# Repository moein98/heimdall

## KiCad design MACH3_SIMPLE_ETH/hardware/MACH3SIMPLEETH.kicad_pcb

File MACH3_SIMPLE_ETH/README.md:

# MACH3-SIMPLE-ETH (draft 0)

MACH3-SIMPLE with Ethernet instead of the parallel ports: an RP2350B runs
grblHAL on the board, eight independent coordinated axes, W5500 Ethernet,
the A1 relays, inputs and isolated VFD port, plus RS485 Modbus, SD card and
a web UI served by the board.

So far: architecture and pin map (`docs/SPEC.md`), a grblHAL build that
proves the pin map, and the schematic (ERC clean, checked against the
firmware's pin map). No board layout yet.

| Folder | What is in it |
|---|---|
| `docs/SPEC.md` | the design, the RP2350B pin map, circuit notes, schematic status |
| `hardware/` | KiCad 10 schematic, 8 sheets - generated, do not edit by hand |
| `tools/` | `build_project.py` (generates the schematic), `check_pinmap.py`, `validate.sh` |
| `review/` | ERC report, netlist, schematic PDF, BOM |
| `firmware/grblHAL/` | board map, `my_machine.h` and CMake patches, `build.sh` |
| `firmware/remora/` | a three-line patch that builds Remora (LinuxCNC) for RP2350 - untested |

    PICO_SDK_PATH=/path/to/pico-sdk sh firmware/grblHAL/build.sh

    python3 tools/build_project.py     # KICAD_SYMBOL_DIR = KiCad's symbol library
    KICAD_CLI=kicad-cli sh tools/validate.sh

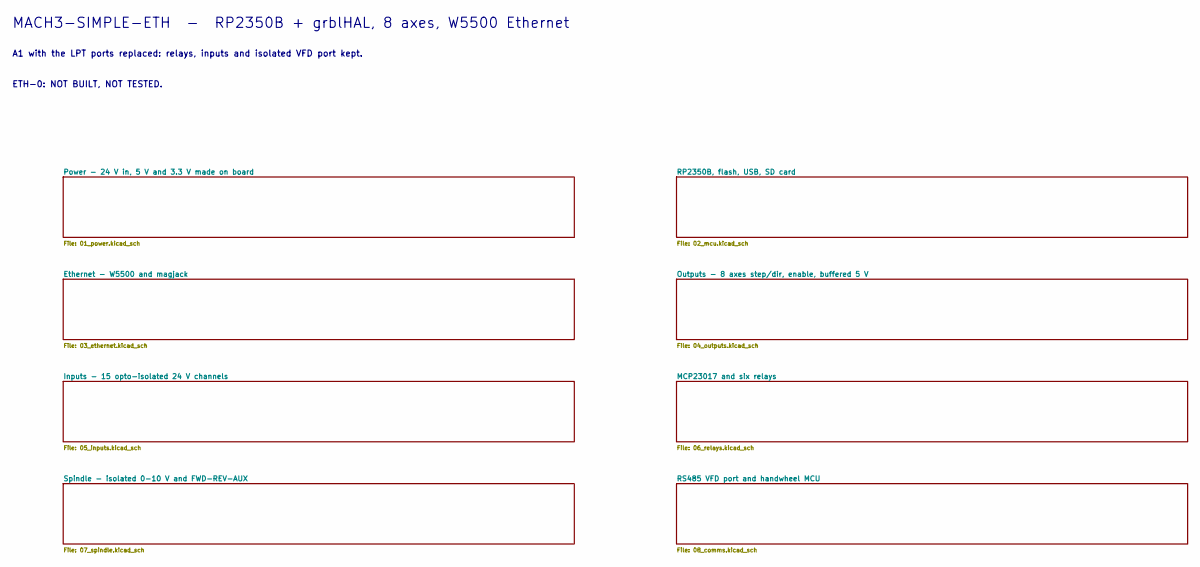
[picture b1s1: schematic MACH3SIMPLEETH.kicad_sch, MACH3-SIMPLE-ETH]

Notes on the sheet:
MACH3-SIMPLE-ETH - RP2350B + grblHAL, 8 axes, W5500 Ethernet
A1 with the LPT ports replaced: relays, inputs and isolated VFD port kept.
ETH-0: NOT BUILT, NOT TESTED.

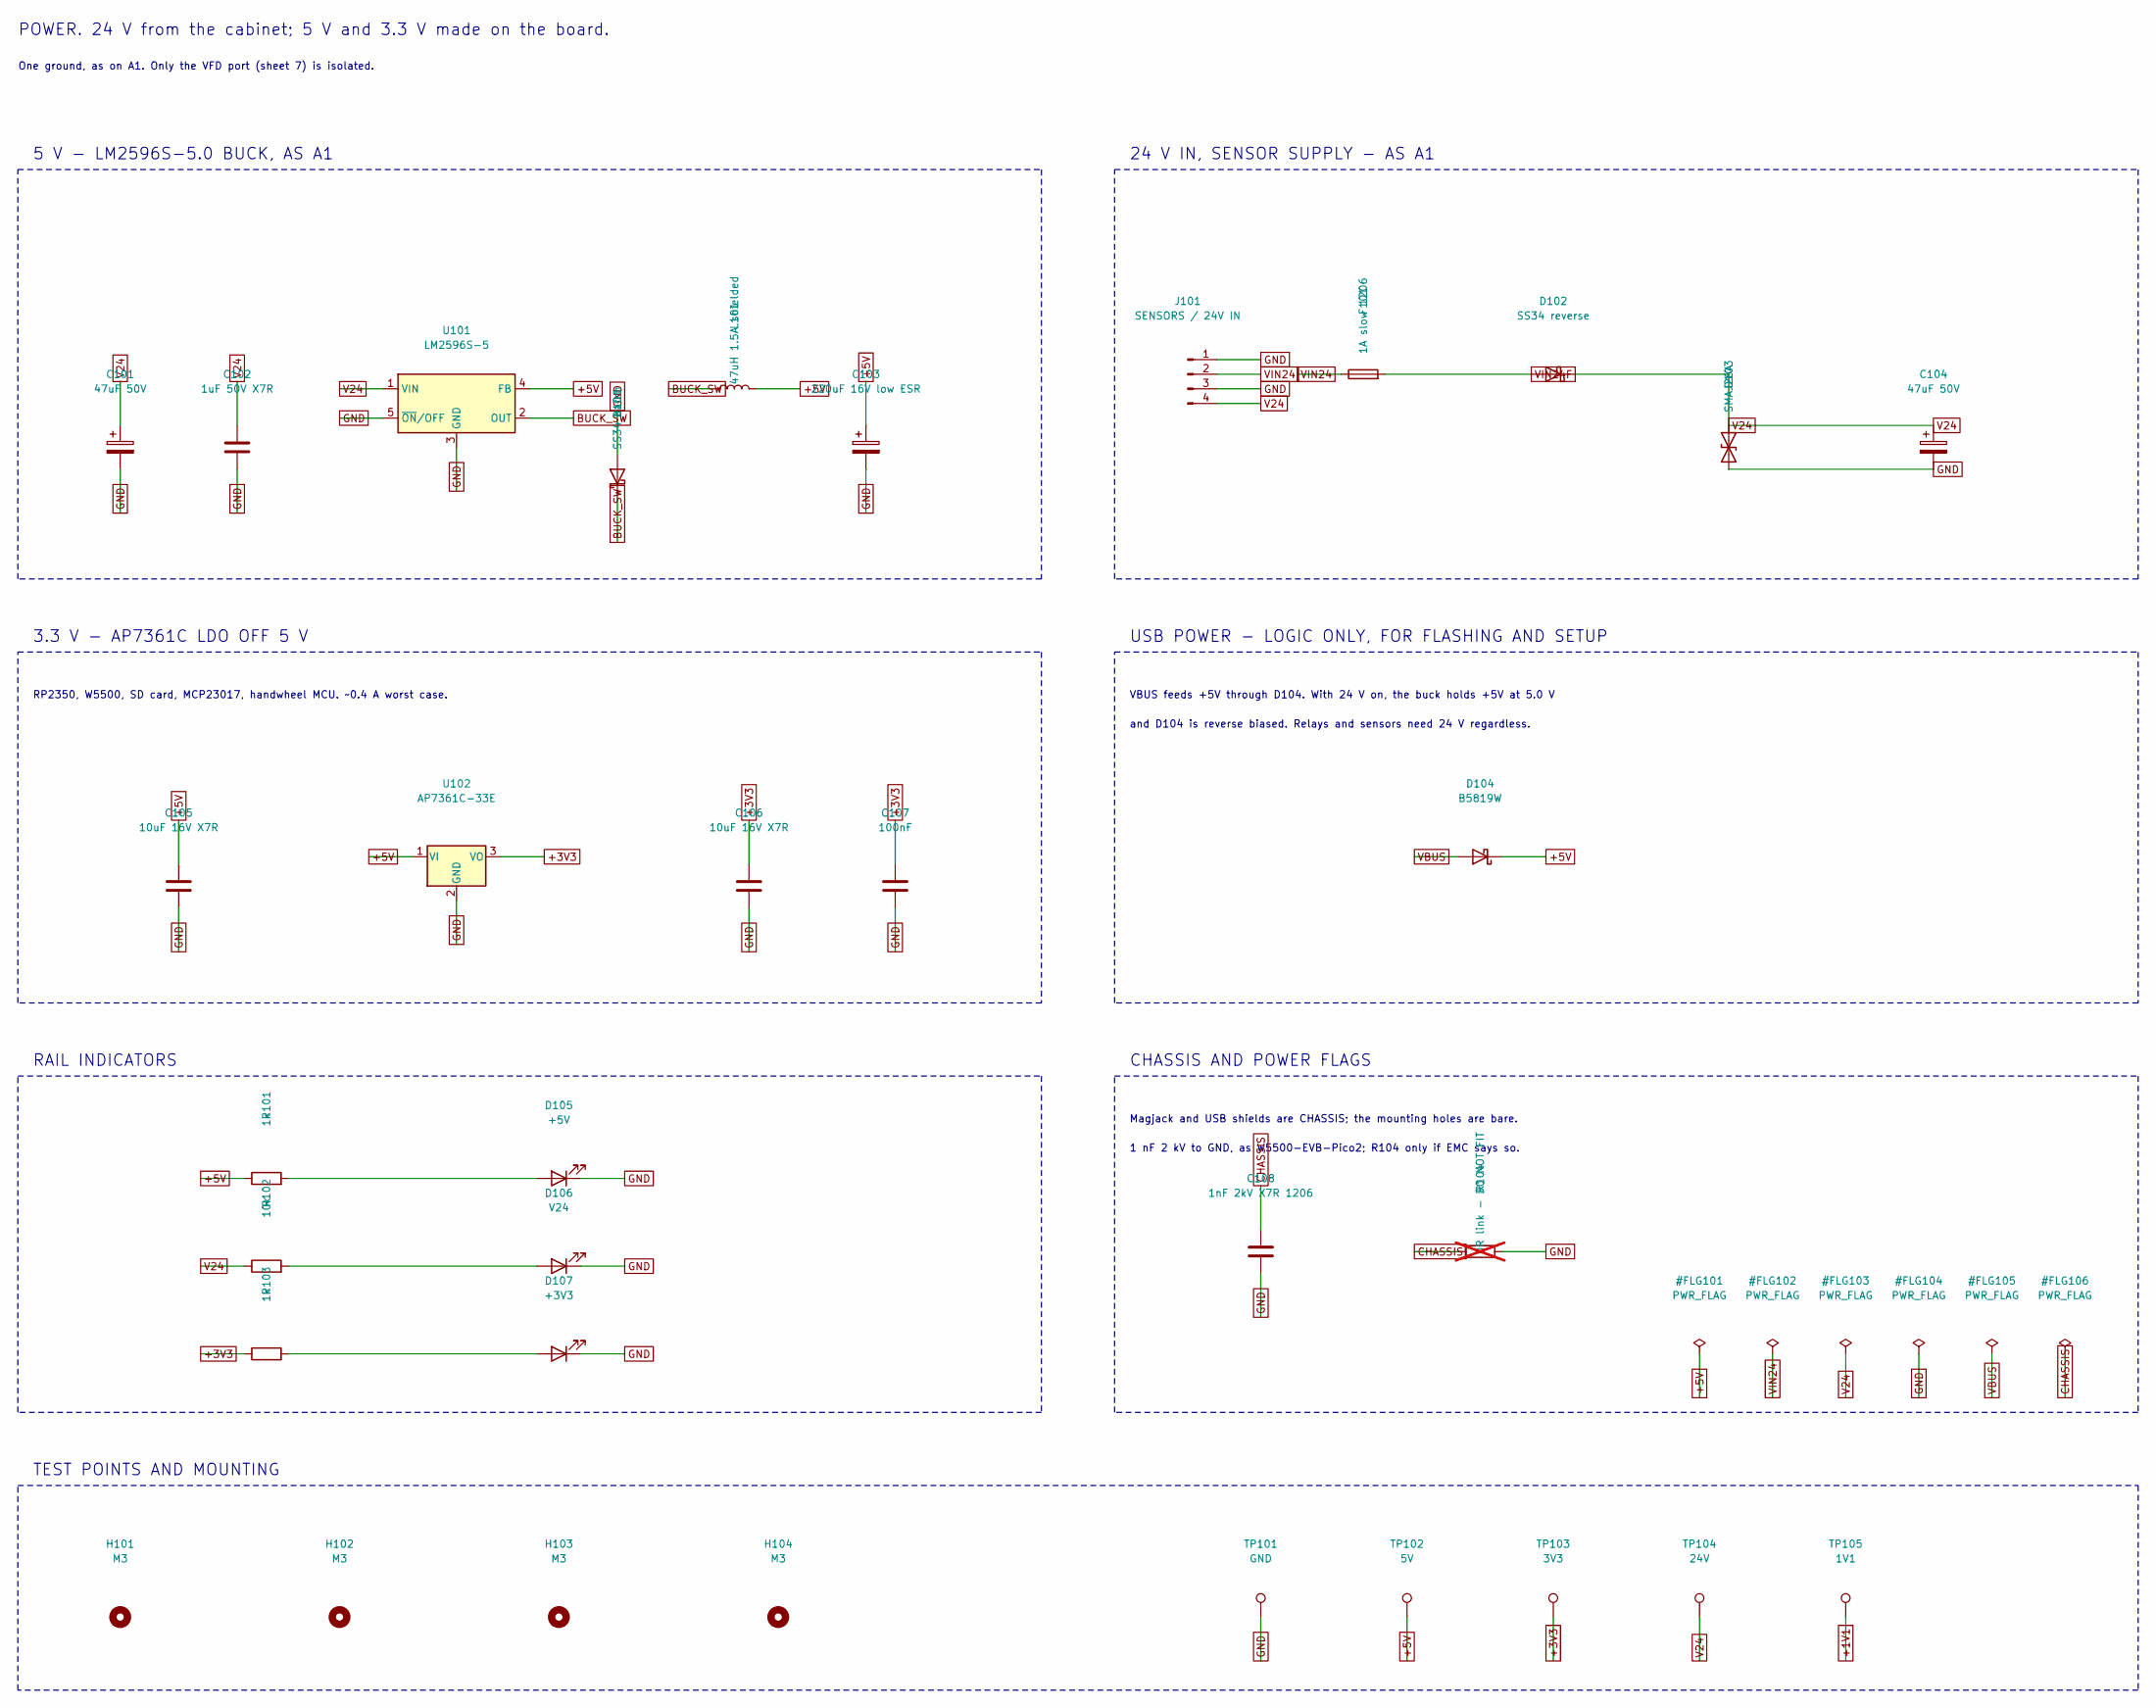
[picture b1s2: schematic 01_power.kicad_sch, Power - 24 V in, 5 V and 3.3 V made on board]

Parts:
C101, C104: 47uF 50V; CP_Elec_6.3x7.7
C102: 1uF 50V X7R; C_1206_3216Metric
C103: 220uF 16V low ESR; CP_Elec_6.3x7.7
C105, C106: 10uF 16V X7R; C_0805_2012Metric
C107: 100nF; C_0603_1608Metric
C108: 1nF 2kV X7R 1206; C_1206_3216Metric
D101: SS34 catch; D_SMA
D102: SS34 reverse; D_SMA
D103: SMAJ26A; D_SMA
D104: B5819W; D_SOD-123
D105: +5V; LED_0603_1608Metric
D106: V24; LED_0603_1608Metric
D107: +3V3; LED_0603_1608Metric
F101: 1A slow 1206; Fuse_1206_3216Metric
H101, H102, H103, H104: M3; MountingHole_3.2mm_M3
J101: SENSORS / 24V IN; TerminalBlock_Phoenix_MKDS-1,5-4_1x04_P5.00mm_Horizontal
L101: 47uH 1.5A shielded; L_12x12mm_H8mm
R101, R103: 1k; R_0603_1608Metric
R102: 10k; R_0603_1608Metric
R104: 0R link - DO NOT FIT; R_1206_3216Metric; not fitted
TP101: GND; TestPoint_THTPad_D2.0mm_Drill1.0mm
TP102: 5V; TestPoint_THTPad_D2.0mm_Drill1.0mm
TP103: 3V3; TestPoint_THTPad_D2.0mm_Drill1.0mm
TP104: 24V; TestPoint_THTPad_D2.0mm_Drill1.0mm
TP105: 1V1; TestPoint_THTPad_D2.0mm_Drill1.0mm
U101: LM2596S-5; TO-263-5_TabPin3
U102: AP7361C-33E; SOT-223-3_TabPin2

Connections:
+1V1: TP105.1; also elsewhere on the board
+3V3: C106.1, C107.1, R103.1, TP103.1, U102.3 (VO); also elsewhere on the board
+5V: C103.1, C105.1, D104.1 (K), L101.2, R101.1, TP102.1, U101.4 (FB), U102.1 (VI); also elsewhere on the board
BUCK_SW: D101.1 (K), L101.1, U101.2 (OUT)
CHASSIS: C108.1, R104.1; also elsewhere on the board
GND: C101.2, C102.2, C103.2, C104.2, C105.2, C106.2, C107.2, C108.2, D101.2 (A), D103.2 (A2), D105.1 (K), D106.1 (K), D107.1 (K), J101.1, J101.3, R104.2, TP101.1, U101.3 (GND), U101.5 (~ON/OFF), U102.2 (GND); also elsewhere on the board
unnamed: D105.2 (A), R101.2
unnamed: D106.2 (A), R102.2
unnamed: D107.2 (A), R103.2
V24: C101.1, C102.1, C104.1, D102.1 (K), D103.1 (A1), J101.4, R102.1, TP104.1, U101.1 (VIN); also elsewhere on the board
VBUS: D104.2 (A); also elsewhere on the board
VIN24: F101.1, J101.2
VIN24F: D102.2 (A), F101.2

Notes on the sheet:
POWER. 24 V from the cabinet; 5 V and 3.3 V made on the board.
One ground, as on A1. Only the VFD port (sheet 7) is isolated.
5 V - LM2596S-5.0 BUCK, AS A1
24 V IN, SENSOR SUPPLY - AS A1
3.3 V - AP7361C LDO OFF 5 V
RP2350, W5500, SD card, MCP23017, handwheel MCU. ~0.4 A worst case.
USB POWER - LOGIC ONLY, FOR FLASHING AND SETUP
VBUS feeds +5V through D104. With 24 V on, the buck holds +5V at 5.0 V
and D104 is reverse biased. Relays and sensors need 24 V regardless.
RAIL INDICATORS
CHASSIS AND POWER FLAGS
Magjack and USB shields are CHASSIS; the mounting holes are bare.
1 nF 2 kV to GND, as W5500-EVB-Pico2; R104 only if EMC says so.
TEST POINTS AND MOUNTING

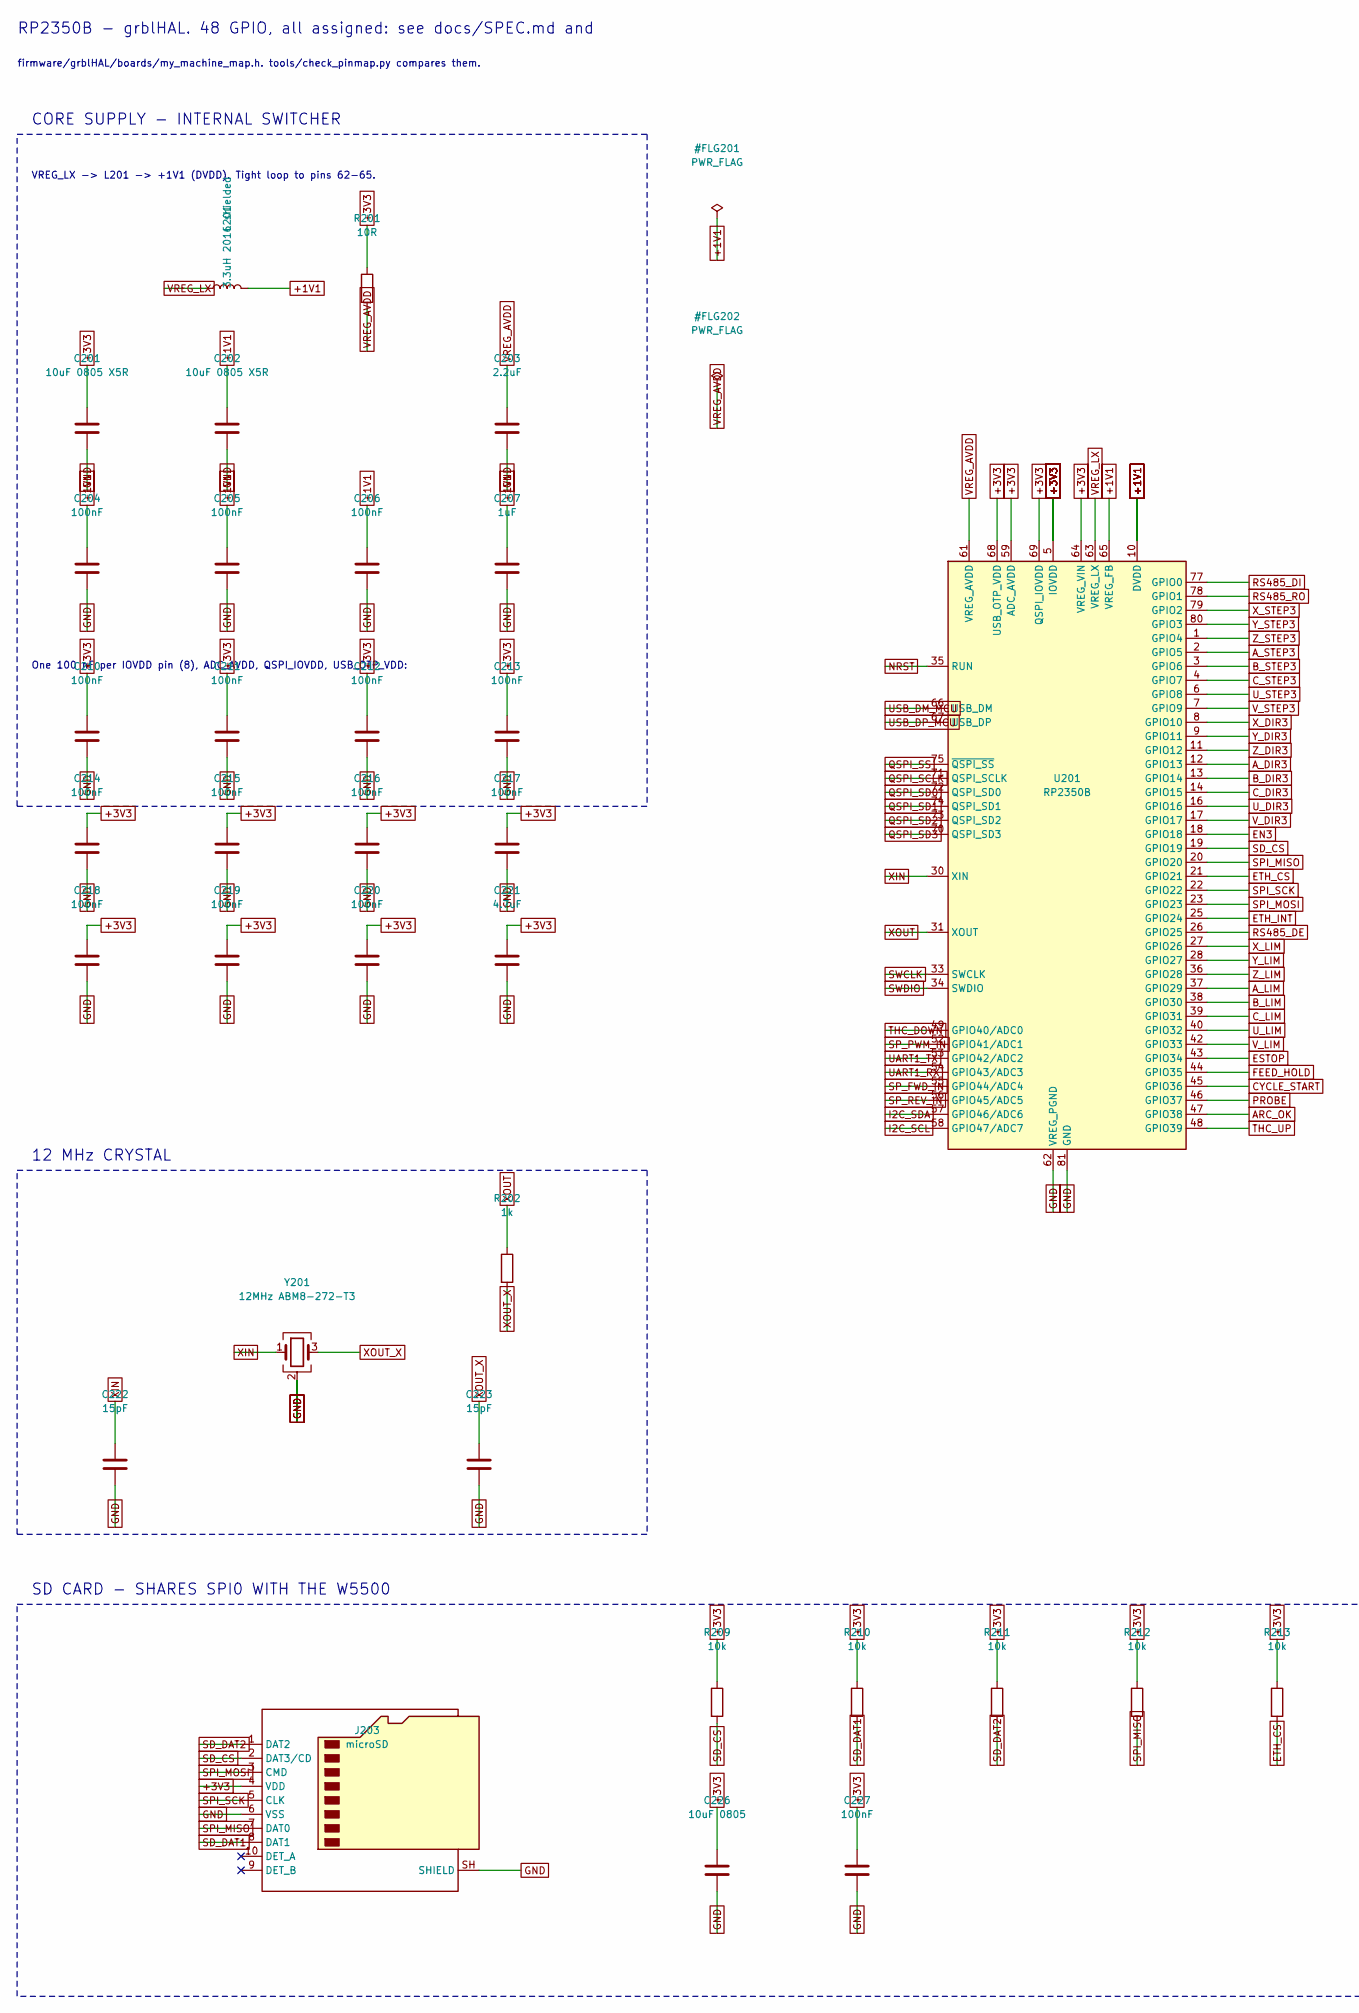
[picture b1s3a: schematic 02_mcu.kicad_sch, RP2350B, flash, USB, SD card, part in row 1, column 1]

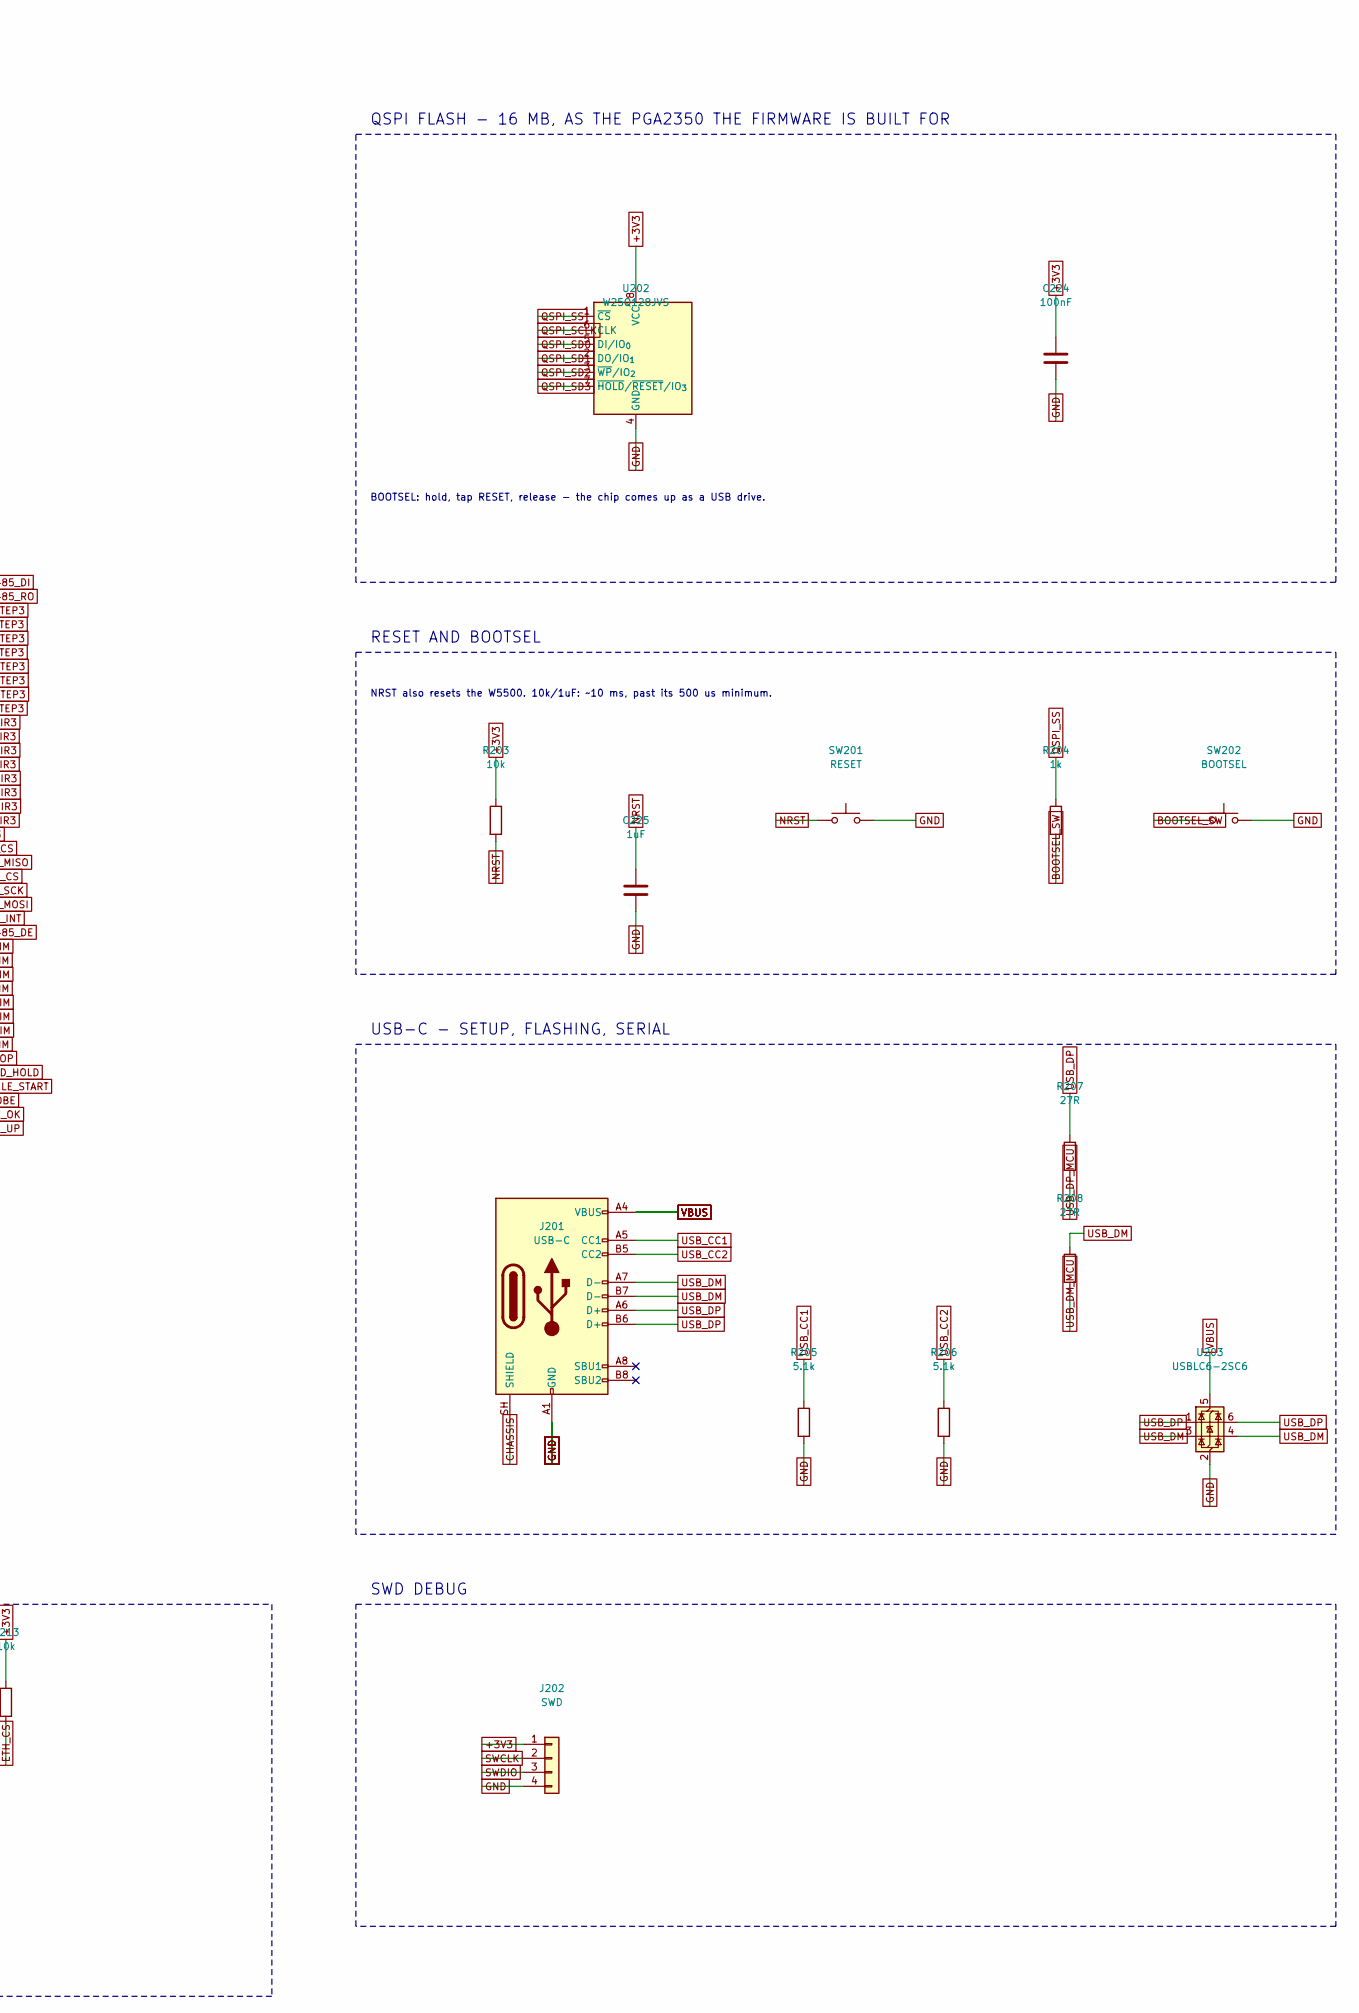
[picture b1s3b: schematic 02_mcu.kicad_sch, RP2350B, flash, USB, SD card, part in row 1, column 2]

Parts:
C201, C202: 10uF 0805 X5R; C_0805_2012Metric
C203: 2.2uF; C_0603_1608Metric
C204, C205, C206, C210, C211, C212, C213, C214, C215, C216, C217, C218, C219, C220, C224, C227: 100nF; C_0603_1608Metric
C207, C225: 1uF; C_0603_1608Metric
C221: 4.7uF; C_0603_1608Metric
C222, C223: 15pF; C_0603_1608Metric
C226: 10uF 0805; C_0805_2012Metric
J201: USB-C; USB_C_Receptacle_HRO_TYPE-C-31-M-12
J202: SWD; PinHeader_1x04_P2.54mm_Vertical
J203: microSD; microSD_HC_Hirose_DM3AT-SF-PEJM5
L201: 3.3uH 2016 shielded; L_Murata_DFE201610P
R201: 10R; R_0603_1608Metric
R202, R204: 1k; R_0603_1608Metric
R203, R209, R210, R211, R212, R213: 10k; R_0603_1608Metric
R205, R206: 5.1k; R_0603_1608Metric
R207, R208: 27R; R_0603_1608Metric
SW201: RESET; SW_SPST_PTS810
SW202: BOOTSEL; SW_SPST_PTS810
U201: RP2350B; QFN-80-1EP_10x10mm_P0.4mm_EP3.4x3.4mm
U202: W25Q128JVS; SOIC-8_5.3x5.3mm_P1.27mm
U203: USBLC6-2SC6; SOT-23-6
Y201: 12MHz ABM8-272-T3; Crystal_SMD_3225-4Pin_3.2x2.5mm

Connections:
+1V1: C202.1, C204.1, C205.1, C206.1, C207.1, L201.2, U201.10 (DVDD), U201.32 (DVDD), U201.51 (DVDD), U201.65 (VREG_FB); also elsewhere on the board
+3V3: C201.1, C210.1, C211.1, C212.1, C213.1, C214.1, C215.1, C216.1, C217.1, C218.1, C219.1, C220.1, C221.1, C224.1, C226.1, C227.1, J202.1, J203.4 (VDD), R201.1, R203.1, R209.1, R210.1, R211.1, R212.1, R213.1, U201.5 (IOVDD), U201.15 (IOVDD), U201.24 (IOVDD), U201.29 (IOVDD), U201.41 (IOVDD), U201.50 (IOVDD), U201.59 (ADC_AVDD), U201.60 (IOVDD), U201.64 (VREG_VIN), U201.68 (USB_OTP_VDD), U201.69 (QSPI_IOVDD), U201.76 (IOVDD), U202.8 (VCC); also elsewhere on the board
ARC_OK: U201.47 (GPIO38); also elsewhere on the board
A_DIR3: U201.12 (GPIO13); also elsewhere on the board
A_LIM: U201.37 (GPIO29); also elsewhere on the board
A_STEP3: U201.2 (GPIO5); also elsewhere on the board
BOOTSEL_SW: R204.2, SW202.1
B_DIR3: U201.13 (GPIO14); also elsewhere on the board
B_LIM: U201.38 (GPIO30); also elsewhere on the board
B_STEP3: U201.3 (GPIO6); also elsewhere on the board
CHASSIS: J201.SH (SHIELD); also elsewhere on the board
CYCLE_START: U201.45 (GPIO36); also elsewhere on the board
C_DIR3: U201.14 (GPIO15); also elsewhere on the board
C_LIM: U201.39 (GPIO31); also elsewhere on the board
C_STEP3: U201.4 (GPIO7); also elsewhere on the board
EN3: U201.18 (GPIO18); also elsewhere on the board
ESTOP: U201.43 (GPIO34); also elsewhere on the board
ETH_CS: R213.2, U201.21 (GPIO21); also elsewhere on the board
ETH_INT: U201.25 (GPIO24); also elsewhere on the board
FEED_HOLD: U201.44 (GPIO35); also elsewhere on the board
GND: C201.2, C202.2, C203.2, C204.2, C205.2, C206.2, C207.2, C210.2, C211.2, C212.2, C213.2, C214.2, C215.2, C216.2, C217.2, C218.2, C219.2, C220.2, C221.2, C222.2, C223.2, C224.2, C225.2, C226.2, C227.2, J201.A1 (GND), J201.A12 (GND), J201.B1 (GND), J201.B12 (GND), J202.4, J203.6 (VSS), J203.SH (SHIELD), R205.2, R206.2, SW201.2, SW202.2, U201.62 (VREG_PGND), U201.81 (GND), U202.4 (GND), U203.2 (GND), Y201.2 (G), Y201.4 (G); also elsewhere on the board
I2C_SCL: U201.58 (GPIO47/ADC7); also elsewhere on the board
I2C_SDA: U201.57 (GPIO46/ADC6); also elsewhere on the board
NRST: C225.1, R203.2, SW201.1, U201.35 (RUN); also elsewhere on the board
PROBE: U201.46 (GPIO37); also elsewhere on the board
QSPI_SCLK: U201.71 (QSPI_SCLK), U202.6 (CLK)
QSPI_SD0: U201.72 (QSPI_SD0), U202.5 (DI/IO_{0})
QSPI_SD1: U201.74 (QSPI_SD1), U202.2 (DO/IO_{1})
QSPI_SD2: U201.73 (QSPI_SD2), U202.3 (~WP/IO_{2})
QSPI_SD3: U201.70 (QSPI_SD3), U202.7 (~HOLD/~RESET/IO_{3})
QSPI_SS: R204.1, U201.75 (~QSPI_SS), U202.1 (~CS)
RS485_DE: U201.26 (GPIO25); also elsewhere on the board
RS485_DI: U201.77 (GPIO0); also elsewhere on the board
RS485_RO: U201.78 (GPIO1); also elsewhere on the board
SD_CS: J203.2 (DAT3/CD), R209.2, U201.19 (GPIO19)
SD_DAT1: J203.8 (DAT1), R210.2
SD_DAT2: J203.1 (DAT2), R211.2
SPI_MISO: J203.7 (DAT0), R212.2, U201.20 (GPIO20); also elsewhere on the board
SPI_MOSI: J203.3 (CMD), U201.23 (GPIO23); also elsewhere on the board
SPI_SCK: J203.5 (CLK), U201.22 (GPIO22); also elsewhere on the board
SP_FWD_IN: U201.55 (GPIO44/ADC4); also elsewhere on the board
SP_PWM_IN: U201.52 (GPIO41/ADC1); also elsewhere on the board
SP_REV_IN: U201.56 (GPIO45/ADC5); also elsewhere on the board
SWCLK: J202.2, U201.33 (SWCLK)
SWDIO: J202.3, U201.34 (SWDIO)
THC_DOWN: U201.49 (GPIO40/ADC0); also elsewhere on the board
THC_UP: U201.48 (GPIO39); also elsewhere on the board
UART1_RX: U201.54 (GPIO43/ADC3); also elsewhere on the board
UART1_TX: U201.53 (GPIO42/ADC2); also elsewhere on the board
USB_CC1: J201.A5 (CC1), R205.1
USB_CC2: J201.B5 (CC2), R206.1
USB_DM: J201.A7 (D-), J201.B7 (D-), R208.1, U203.3 (I/O2), U203.4 (I/O2)
USB_DM_MCU: R208.2, U201.66 (USB_DM)
USB_DP: J201.A6 (D+), J201.B6 (D+), R207.1, U203.1 (I/O1), U203.6 (I/O1)
USB_DP_MCU: R207.2, U201.67 (USB_DP)
U_DIR3: U201.16 (GPIO16); also elsewhere on the board
U_LIM: U201.40 (GPIO32); also elsewhere on the board
U_STEP3: U201.6 (GPIO8); also elsewhere on the board
VBUS: J201.A4 (VBUS), J201.A9 (VBUS), J201.B4 (VBUS), J201.B9 (VBUS), U203.5 (VBUS); also elsewhere on the board
VREG_AVDD: C203.1, R201.2, U201.61 (VREG_AVDD)
VREG_LX: L201.1, U201.63 (VREG_LX)
V_DIR3: U201.17 (GPIO17); also elsewhere on the board
V_LIM: U201.42 (GPIO33); also elsewhere on the board
V_STEP3: U201.7 (GPIO9); also elsewhere on the board
XIN: C222.1, U201.30 (XIN), Y201.1
XOUT: R202.1, U201.31 (XOUT)
XOUT_X: C223.1, R202.2, Y201.3
X_DIR3: U201.8 (GPIO10); also elsewhere on the board
X_LIM: U201.27 (GPIO26); also elsewhere on the board
X_STEP3: U201.79 (GPIO2); also elsewhere on the board
Y_DIR3: U201.9 (GPIO11); also elsewhere on the board
Y_LIM: U201.28 (GPIO27); also elsewhere on the board
Y_STEP3: U201.80 (GPIO3); also elsewhere on the board
Z_DIR3: U201.11 (GPIO12); also elsewhere on the board
Z_LIM: U201.36 (GPIO28); also elsewhere on the board
Z_STEP3: U201.1 (GPIO4); also elsewhere on the board

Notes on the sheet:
RP2350B - grblHAL. 48 GPIO, all assigned: see docs/SPEC.md and
firmware/grblHAL/boards/my_machine_map.h. tools/check_pinmap.py compares them.
CORE SUPPLY - INTERNAL SWITCHER
VREG_LX -> L201 -> +1V1 (DVDD). Tight loop to pins 62-65.
One 100 nF per IOVDD pin (8), ADC_AVDD, QSPI_IOVDD, USB_OTP_VDD:
12 MHz CRYSTAL
QSPI FLASH - 16 MB, AS THE PGA2350 THE FIRMWARE IS BUILT FOR
BOOTSEL: hold, tap RESET, release - the chip comes up as a USB drive.
RESET AND BOOTSEL
NRST also resets the W5500. 10k/1uF: ~10 ms, past its 500 us minimum.
USB-C - SETUP, FLASHING, SERIAL
SWD DEBUG
SD CARD - SHARES SPI0 WITH THE W5500

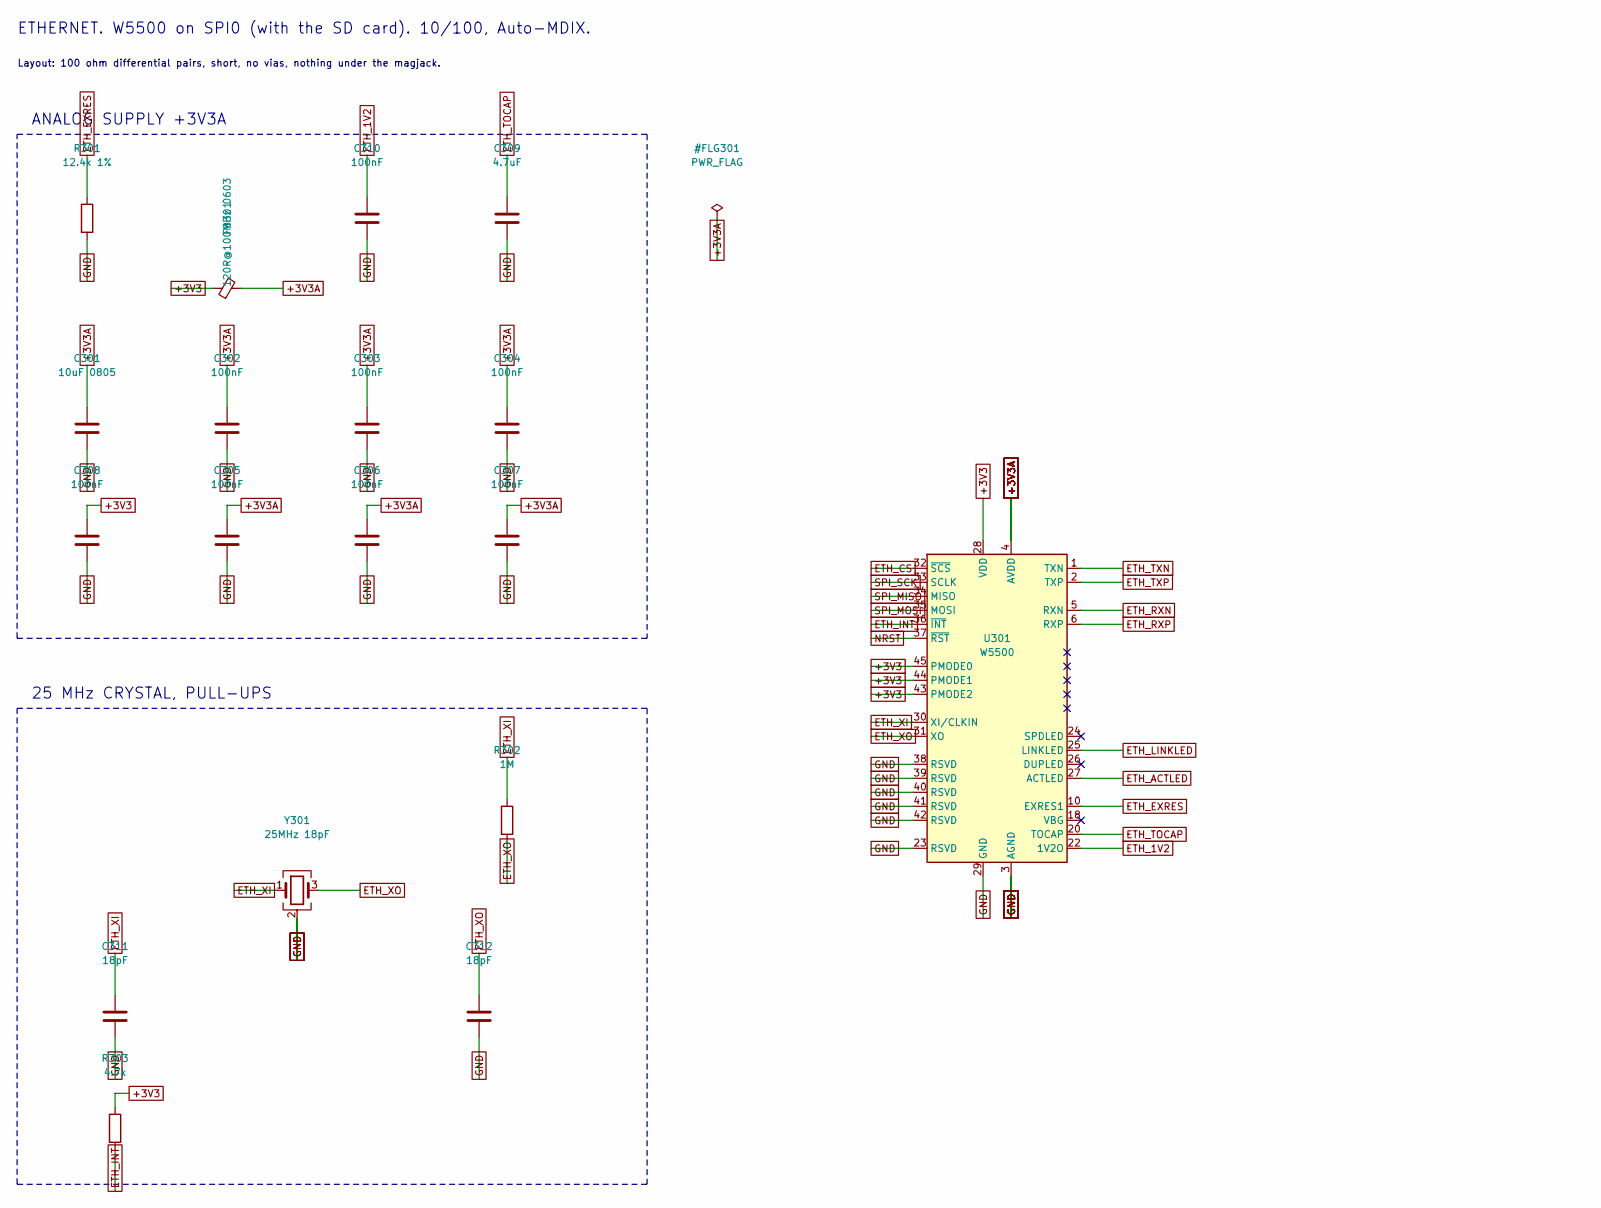
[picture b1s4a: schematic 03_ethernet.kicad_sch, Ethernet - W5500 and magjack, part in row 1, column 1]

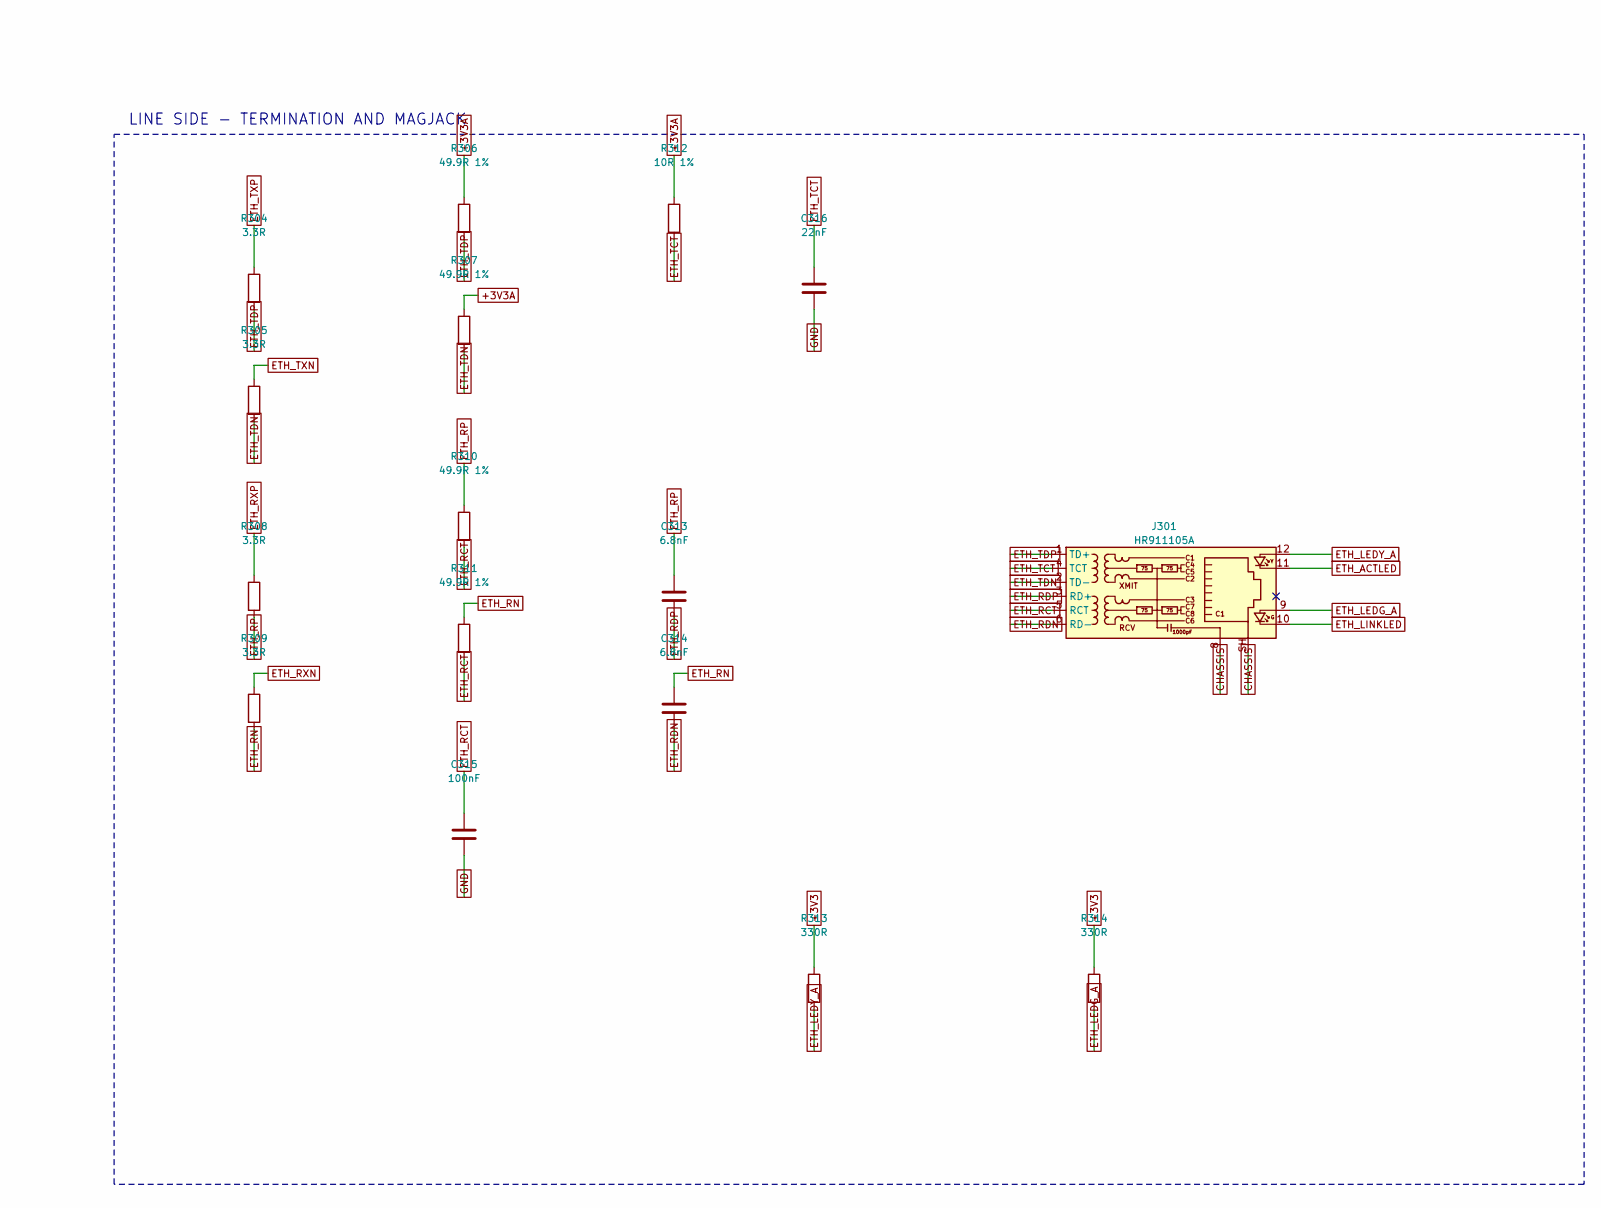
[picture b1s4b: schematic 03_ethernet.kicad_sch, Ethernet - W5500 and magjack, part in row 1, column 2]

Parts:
C301: 10uF 0805; C_0805_2012Metric
C302, C303, C304, C305, C306, C307, C308, C310, C315: 100nF; C_0603_1608Metric
C309: 4.7uF; C_0603_1608Metric
C311, C312: 18pF; C_0603_1608Metric
C313, C314: 6.8nF; C_0603_1608Metric
C316: 22nF; C_0603_1608Metric
FB301: 120R@100MHz 0603; L_0603_1608Metric
J301: HR911105A; RJ45_Hanrun_HR911105A_Horizontal
R301: 12.4k 1%; R_0603_1608Metric
R302: 1M; R_0603_1608Metric
R303: 4.7k; R_0603_1608Metric
R304, R305, R308, R309: 3.3R; R_0603_1608Metric
R306, R307, R310, R311: 49.9R 1%; R_0603_1608Metric
R312: 10R 1%; R_0603_1608Metric
R313, R314: 330R; R_0603_1608Metric
U301: W5500; LQFP-48_7x7mm_P0.5mm
Y301: 25MHz 18pF; Crystal_SMD_3225-4Pin_3.2x2.5mm

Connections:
+3V3: C308.1, FB301.1, R303.1, R313.1, R314.1, U301.28 (VDD), U301.43 (PMODE2), U301.44 (PMODE1), U301.45 (PMODE0); also elsewhere on the board
+3V3A: C301.1, C302.1, C303.1, C304.1, C305.1, C306.1, C307.1, FB301.2, R306.1, R307.1, R312.1, U301.4 (AVDD), U301.8 (AVDD), U301.11 (AVDD), U301.15 (AVDD), U301.17 (AVDD), U301.21 (AVDD)
CHASSIS: J301.8, J301.SH; also elsewhere on the board
ETH_1V2: C310.1, U301.22 (1V2O)
ETH_ACTLED: J301.11, U301.27 (ACTLED)
ETH_CS: U301.32 (~SCS); also elsewhere on the board
ETH_EXRES: R301.1, U301.10 (EXRES1)
ETH_INT: R303.2, U301.36 (~INT); also elsewhere on the board
ETH_LEDG_A: J301.9, R314.2
ETH_LEDY_A: J301.12, R313.2
ETH_LINKLED: J301.10, U301.25 (LINKLED)
ETH_RCT: C315.1, J301.5 (RCT), R310.2, R311.2
ETH_RDN: C314.2, J301.6 (RD-)
ETH_RDP: C313.2, J301.3 (RD+)
ETH_RN: C314.1, R309.2, R311.1
ETH_RP: C313.1, R308.2, R310.1
ETH_RXN: R309.1, U301.5 (RXN)
ETH_RXP: R308.1, U301.6 (RXP)
ETH_TCT: C316.1, J301.4 (TCT), R312.2
ETH_TDN: J301.2 (TD-), R305.2, R307.2
ETH_TDP: J301.1 (TD+), R304.2, R306.2
ETH_TOCAP: C309.1, U301.20 (TOCAP)
ETH_TXN: R305.1, U301.1 (TXN)
ETH_TXP: R304.1, U301.2 (TXP)
ETH_XI: C311.1, R302.1, U301.30 (XI/CLKIN), Y301.1
ETH_XO: C312.1, R302.2, U301.31 (XO), Y301.3
GND: C301.2, C302.2, C303.2, C304.2, C305.2, C306.2, C307.2, C308.2, C309.2, C310.2, C311.2, C312.2, C315.2, C316.2, R301.2, U301.3 (AGND), U301.9 (AGND), U301.14 (AGND), U301.16 (AGND), U301.19 (AGND), U301.23 (RSVD), U301.29 (GND), U301.38 (RSVD), U301.39 (RSVD), U301.40 (RSVD), U301.41 (RSVD), U301.42 (RSVD), U301.48 (AGND), Y301.2 (G), Y301.4 (G); also elsewhere on the board
NRST: U301.37 (~RST); also elsewhere on the board
SPI_MISO: U301.34 (MISO); also elsewhere on the board
SPI_MOSI: U301.35 (MOSI); also elsewhere on the board
SPI_SCK: U301.33 (SCLK); also elsewhere on the board

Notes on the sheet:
ETHERNET. W5500 on SPI0 (with the SD card). 10/100, Auto-MDIX.
Layout: 100 ohm differential pairs, short, no vias, nothing under the magjack.
ANALOG SUPPLY +3V3A
25 MHz CRYSTAL, PULL-UPS
LINE SIDE - TERMINATION AND MAGJACK
